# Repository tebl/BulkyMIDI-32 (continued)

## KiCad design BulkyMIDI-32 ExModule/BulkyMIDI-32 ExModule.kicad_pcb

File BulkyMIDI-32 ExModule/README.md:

# BulkyMIDI-32 ExModule
The *BulkyMIDI-32* consists of several separate designs with the same styling, the *ExModule* specifically allows you to use modern Wavetable-modules such as those sold by serdashop.com (not affiliated with this project). Normally these would be installed onto a compatible vintage soundcard, but as it turns out - the machine I wanted to install one on had an AWE32 without the actual header - so instead of changing out the soundcard I built this instead.

What this actually does is add the circuitry that is needed to use them with any MIDI-capable soundcard, externally over a MIDI-cable. Check out the [getting started](https://github.com/tebl/BulkyMIDI-32/blob/main/documentation/getting_started.md) part of the documentation, and while the text mainly covers the *BulkyMIDI-32* (Roland MT-32 emulation via mt32-pi) itself - it's all MIDI, and it should work just about the same. The only difference is that with the *ExModule* you'll be using real modules instead of emulating them.

As for what it looks like inside, there's really not a lot that is needed to make it work - and I was able to assemble most of it thank to the details still available on [atari.joska.no](https://atari.joska.no/db50xg/). While the page focuses on the Atari ST, the specifics are really the same regardless of platform. The source of his designs was based on an article in Elektor Electronics (july/august 1997), but as all of their articles have been permanently locked behind a paywall - I can't link you to a copy of it. In either case I more or less changed just about everything to use similar components as those featured elsewhere in this repository.

**NB!** This module only takes a 5V input, and does not have any way of generating the remaining voltages required by some vintage Wavetable-modules. There are references to a Power-module that could be created to provide those, but I don't have anything to test with it. Unless someone straight up gifts my one of their vintage modules to test with it, it won't be added.

- [1> Building the device](#1-building-the-device)
  - [1.1> Soldering it together](#11-soldering-it-together)
  - [1.2> Without front panel](#12-without-front-panel)
  - [1.3> Including front panel](#13-including-front-panel)
  - [1.4> Finishing touches](#14-finishing-touches)
- [2> Schematic](#2-schematic)
- [3> BOM](#3-bom)

# 1> Building the device
Building a device such as this assumes you have at least minor experience soldering things together, recommended is that you at the very least have access to a soldering station with adjustable temperature. If currently available, you should probably start with 60/40 rosin core solder as the lead-free alternatives tends to be a bit harder to work with.

With requirements for basic equipment sorted, we need to talk a bit about what you want to achieve while building this project. The reason I ask is that while you can build a functional *BulkyMIDI-32 ExModule* by using this module by itself, but there is certainly the option of building the complete version of it - that includes the front panel as well as two faceplates, one that goes on top of the device and one that mounts on the front. 

Now that you know what you want to build, we can get started on the most expensive step in any build process - shopping! So, head on over to the [BOM](#3-bom)-section for some information on what kind of components that you'll need. While I would have liked to give you specific part numbers for "reputable" electronic part suppliers, I can't afford to shop there myself. For that reason I usually make due with what I can find on sites such as ebay, AliExpress and any similar sites that sells affordable Chinese components. The downside to this is that I can't link to a part directly and expect it to stay listed beyond the next couple of days, so you'll need to think of the descriptions listed as *suggested search terms* instead of part numbers.

## 1.1> Soldering it together
The construction of this unit should be fairly straight-forward, just take your time in order to make sure everything goes into place - more or less straight. I usually recommend starting by having a good look at the PCBs, try to figure out where all of the listed components go and in which orientation they go in (most of the information should be clearly marked on the silkscreen).

I will usually try to install components sorted by their physical size, doing it this way means you'll have an easier time keeping everything from looking somewhat crooked. This is your board, your build and you want it perfect - don't you? If you said no, then go sit in the corner because I worked hard on creating this for myself and whoever wants to build one.

Here we've already gotten started by installing all of the resistors needed, making sure that we use the correct values for each position on the board. While doing this, it is always a good recommendation to try and keep the colour bands orientated the same way - mostly because it makes it easier to spot any mistakes later on. The two that goes in the bottom left corner goes to the LEDs, regardless of whether they are mounted here on the front panel. The values for these need to be adjusted according to the type and colour of the LEDs that you are using, in particular when using one that hasn't been dyed to a specific colour - then you will usually need to increase this value to something like 2k2 to avoid blinding yourself by looking at them.

Two different types of diodes are used, the 1N5819 is a Schottky diode and has a silver stripe on it that needs to be matched up with the markings on the board. The 1N4148 diode is probably more familiar to most, it similarly has a black band that instead denotes how to install it on the board.

Sockets should always be installed for the ICs, especially now that there are a lot of bad components floating around. It's always easier to solder something in that it is to remove them, so consider them a cheap insurance. With the sockets in place I've also installed the monolithic disc capacitors, these are all unpolarized and for the ones without any specific markings we will install 100nF capacitors (the code *104* will be printed on them). The single capacitor marked *C3* has a different value from the others, it is 10nF and will have the code *103* printed on it.

The next component we're going to install is a single *2n3906* PNP-transistors, these have a flat side and a round side that needs to be matched to what is printed on the silkscreen. While there are components available that have pre-bent legs matching those on the footprint, I've not come across them at a reasonable price - so I just bend the legs outward myself and firmly push down on them until they sit a bit above the board. They tend to twist a bit when pushing them into place, that is OK to a certain degree and you generally shouldn't force them too much.

Next up are the polarized capacitors, these need to go in the right way for them to function as expected. The stripe on the side of the capacitor denotes the negative side of it, this should be matched up with the filled in area of the footprint. When in doubt, just put the longer pin into the other hole (marked with a "+"). For the most part we won't be anywhere near any relevant voltage ratings, but note that the higher rated ones will generally be physically larger so don't go overboard without measuring - a 16v rating should be enough for our purposes.

Note that the value of capacitor **C2** directly affects the timing of the missing pulse detector, the circuit that ensures that the activity remains solid instead of blinking (as long as we regularly receive data). If you want something that blinks more vigorously, lower the value to *1 uF*. The formula for calculating the timing used is  T = 1.1 * R1 * C2, which for the specified values means that we keep the LED on as long as we don't see any gaps that are longer than 0.33 seconds. Active MIDI keep-alive messages on more modern equipment is commonly sent out intervals of around 300ms, so that is the rationale for choosing a these specific values.

I designed the board for a PJ-307 3.5mm stereo audio sockets, but the similar PJ-317 may be used as well - both of these are common 5-pin sockets sold just about everywhere. While I've preferred to use green ones for audio output in other parts of the *BulkyMIDI-32* project, I didn't have one available and so I used this black one instead. Just don't confuse them with TRS-type A/B MIDI-cables.

Adding the star of the show, the actual Wavetable-header - you may be slightly disappointed by the fact that it is just a segment of dual-row straight pin headers with a 2.54mm spacing. For power we're using a common DC barrel connector (5.5mm x 2.1mm) that have been soldered to the board, it is recommended that you only solder one of the pins at first so that you are able to reheat and reposition it if needed.

Adding the actual MIDI-connectors is next, these are 5-pin DIN connectors that are used for many purposes - they'll be cheaper when not explicitly listed as a "MIDI-connector" (just a tip). Of the two, only the one marked *MIDI IN* is required. The second is marked *MIDI THRU*, it sends out a copy of the same data that was received by this device (without any kind of processing) - installing it allows you to also have a [Channel Monitor](https://github.com/tebl/BulkyMIDI-32/tree/main?tab=readme-ov-file#13-bulkymidi-32-channel-monitor) connected for some nifty effects. 

If you've been following along, there's an empty spot marked *FB1* that could potentially take one of these small wired ferrite cores. I'm not sure if it is needed, but as the analog and digital grounds will have been connected on the modules themselves - I've simply skipped installing them here. That may be a good choice, or a bad one depending on what you're using it with. The good news is that you have the option to choose differently from me if you're able to tell the difference, because I can't.

Depending on your life decisions up to this point, the assembly from this point continues in one of two directions:
- [1.2> Without front panel](#12-without-front-panel)
- [1.3> Including front panel](#13-including-front-panel)

## 1.2> Without front panel
So you resisted the temptation to build the complete version, choosing instead to cut corners where possible? Well, that's OK too! I'm not judging, it was merely just a general observation.

There's not much that we need to do, mainly just install the two 5mm LED (the shorter leg of the LED goes into the hole with the square pad). Also install a right-angle switch.

If you have a faceplate, the board that goes on top of the device, make sure to add some 20mm hex standoffs to each of the four corners before continuing on to with the next part of the build.

- [1.4> Finishing touches](#14-finishing-touches)

## 1.3> Including front panel

The [ExModule Panel](https://github.com/tebl/BulkyMIDI-32/tree/main/BulkyMIDI-32%20ExModule%20Panel) have its own set of documentation going into the various steps required to put it together correctly, a mostly finished unit should look like what is shown above. In particular we need to ensure that the hex standoffs have been aligned so that a *flat* side is lined up with the left and right edges of the board, the nuts on the back needs to have a similar flat side matched to the top and bottom. You may need to trim these slightly with a sharp knife or a file. 

Starting with installing 20mm standoffs to each of the four corners, making sure that these have a *flat* side pointing towards the inside of the PCB. With the alignment correct you should be able to insert the panel into the board without too much force, then your selected top faceplate is installed on top of the boards using temporary screws.

Note that at this point we've not actually soldered them together yet, mostly to ensure that everything comes together correctly before we attempt to actually do so. Push the panel firmly so that it sits towards the back of the cutouts, then solder the pins into place. Afterwards we just trim the excess parts of the pin headers using some proper wire cutters, a flush-cut pair of pliers will usually just break if you use them for pin headers as the metal is too hard for them to reliably work with. When done, I recommend that you reflow all of the joints in case we cracked one of them while cutting of the pins.

When soldered, everything should stay where it is supposed to be. Before continuing on we just remove the faceplate again before moving on to the next step.

- [1.4> Finishing touches](#14-finishing-touches)

## 1.4> Finishing touches

If you've made it this far, you're almost ready to simply start using it. What's missing in order to test it is the actual ICs that needs to be inserted into their sockets, so just get that out of the way before you forget to do so - the indent of the socket should be matched to pin 1 of your ICs, there they will either have a matching indent or a dot next to pin 1.

The device is powered using a 5v DC barrel jack (center positive). Such a power supply should be easy to obtain from your favourite electronics vendor, just make sure that it's from a company that's at least somewhat respected. Personally I'm using a *MEAN WELL GST25B05-P1J*, but that may not be directly applicable to you due to this specific model having been made with a Europlug on it.

At this point in the installation it may be tempting to just plug a Wavetable-module into it and start sending it some MIDI-data, but it may serve you better to be a bit more prudent. Plugging it into power by itself might allow it to blow up by itself instead of taking something *vintage* along with it, then introduce a modern MIDI-interface such as the Roland UM-ONE and have something attempt to send it data - see [getting started](https://github.com/tebl/BulkyMIDI-32/blob/main/documentation/getting_started.md) for something more specific than what'll be provided for in this document. Once you can see that activity lights up according to what can be expected, meaning that it should light up as solid because a modern interface will continuously send it *keep-alive*-messages.

Once satisfied that you're willing to risk a module, connect it up as shown above - preferably the *cheapest*, or just the one you consider easiest to replace! Make sure that you're not offsetting the pins in either of the directions when installing them, I don't know what would happen - but - I assume it won't be a *fun* experience. Repeat tests done earlier, hook up the stereo to an amplifier and you should be able to enjoy some music from your chosen module.

The only step that's remaining is to just screw the faceplates back on the top of the device, replacing those on the front if you have not already done so. With that done we're ready to start planning your next project, maybe a [BulkyMIDI-32 Channel Monitor](https://github.com/tebl/BulkyMIDI-32/tree/main/BulkyMIDI-32%20Channel) for something more exciting to look at or the [BulkyMIDI-32 Play](https://github.com/tebl/BulkyMIDI-32/tree/main/BulkyMIDI-32%20Play) so that you can listen to MIDI-files without a computer attached to it.

# 2> Schematic
The supplied KiCad files should be sufficient as both a schematic and as a  starting point for ordering PCBs (basically you could just zip the contents of the export folder and upload that on a fabrication site), the schematic is also available in [PDF-format](https://github.com/tebl/BulkyMIDI-32/tree/main/documentation/schematic) and this is what you'll need to print and work your way through this things don't work as expected after assembly.

# 3> BOM
Most parts should be easy to get a hold of from your favourite local electronic component shop, but given that I don't have access to such shops where I live so everything was based on whatever I could get cheapest from eBay/AliExpress (free shipping, but plan on waiting 3-4 weeks for delivery). Components in parenthesis are either optional components, or they will only be installed in certain cases such as having functionally been moved to the [front panel](https://github.com/tebl/BulkyMIDI-32/tree/main/BulkyMIDI-32%20ExModule%20Panel). Note that the panel also has its own BOM, make sure to check that out as well when you're ordering parts.

| Reference             | Item                                                              | Count | Order  |
| --------------------- | ----------------------------------------------------------------- | ----- | ------ |
| PCB                   | Fabricate using Gerber files                                      |     1 | [PCBWay](https://www.pcbway.com/project/shareproject/BulkyMIDI_32_ExModule_6564c365.html)
| [Front Panel](https://github.com/tebl/BulkyMIDI-32/tree/main/BulkyMIDI-32%20ExModule%20Panel) | Fabricate using Gerber files                                      |    (1) | [PCBWay](https://www.pcbway.com/project/shareproject/BulkyMIDI_32_ExModule_Panel_8050038f.html)
| [Front Faceplate](https://github.com/tebl/BulkyMIDI-32/tree/main/faceplates/BulkyMIDI-32%20ExModule%20FP1) | Fabricate using Gerber files                                      |    (1) | [PCBWay](https://www.pcbway.com/project/shareproject/BulkyMIDI_32_ExModule_Faceplate_FP1_640ef0bc.html)
| [Top Faceplate](https://github.com/tebl/BulkyMIDI-32/tree/main/faceplates/BulkyMIDI-32%20FB2) | Fabricate using Gerber files                                      |    (1) | PCBWay
| C1,C4,C5,C7,C9        | 100nF (104) ceramic capacitor (5mm)                               |     5 |
| C2                    | 3.3uF electrolytic capacitor (5mm x 2mm)                          |     1 |
| C3                    | 10nF (103) ceramic capacitor (5mm)                                |     1 |
| C6                    | 470uF electrolytic capacitor (8mm x 3.5mm)                        |     1 |
| C8                    | 10uF electrolytic capacitor (5mm x 2mm)                           |     1 |
| D1,D2 *               | 5mm LED, preferably diffused variety                              |    (2)|
| D3                    | 1N4148N small signal diode (DO-35)                                |     1 |
| D4                    | 1N5819 Schottky diode (DO-41)                                     |     1 |
| FB1                   | Wired ferrite core (probably not needed)                          |    (1)|
| J1                    | 2.1mm x 5.5mm barrel plug                                         |     1 |
| J2                    | Dual-row straight pin header                                      |     1 |
| J3,J5                 | Female S-terminal 5pin DIN PCB                                    |  1 (1)|
| J4                    | PJ-307 3.5mm audio connector (5-pin TRS), (alternatively PJ-317)  |     1 |
| Q1                    | 2N3906 PNP-transistor (TO-92)                                     |     1 |
| R1                    | 100k ohm resistor                                                 |     1 |
| R2                    | 10k ohm resistor                                                  |     1 |
| R3                    | 1M ohm resistor                                                   |     1 |
| R4,R5 **              | 470 ohm resistor                                                  |     2 |
| R6,R10,R18            | 220 ohm resistor                                                  |     3 |
| R7                    | 47k ohm resistor                                                  |     1 |
| R8                    | 1k ohm resistor                                                   |     1 |
| R19                   | 2k2 ohm resistor                                                  |     1 |
| SW1 *                 | 6x6x5mm right-angle momentary button                              |    (1)|
| U1                    | 74HCT14 (DIP-14)                                                  |     1 |
| U2,U4                 | 555 (DIP-8)                                                       |     2 |
| U3                    | 6N138 optocoupler (DIP-8)                                         |     1 |
| Mounting ***          | Nylon M3 hex standoffs 20mm (M-F)                                 |     4 |
| Mounting ***          | Nylon M3x6mm nylon screws                                         |     4 |
| Mounting ***          | Nylon M3x6mm nylon nuts                                           |     4 |

*) You can choose to install a front panel, in which case you would skip the installation of the 5mm LEDs as well as the reset switch. Resistors R4/R5 will still be used by the front panel.
**) Resistors are used with LEDs, either installed here or on the front panel. As the choice of LED type and colour dictates the value of resistor, you need to pick something that is suitable here. If using modern bright LEDs, you will need to increase the value to at least 2k2 in order to have something that isn't considered uncomfortably bright.
***) These are available in the form of kits usually advertised *M3 nylon standoff kit* which should contain most of what you'd need. I do however recommend that you pick up extra M-F standoffs of lengths 8mm and 20mm, as quite a lot of them will be used when building more than one module.

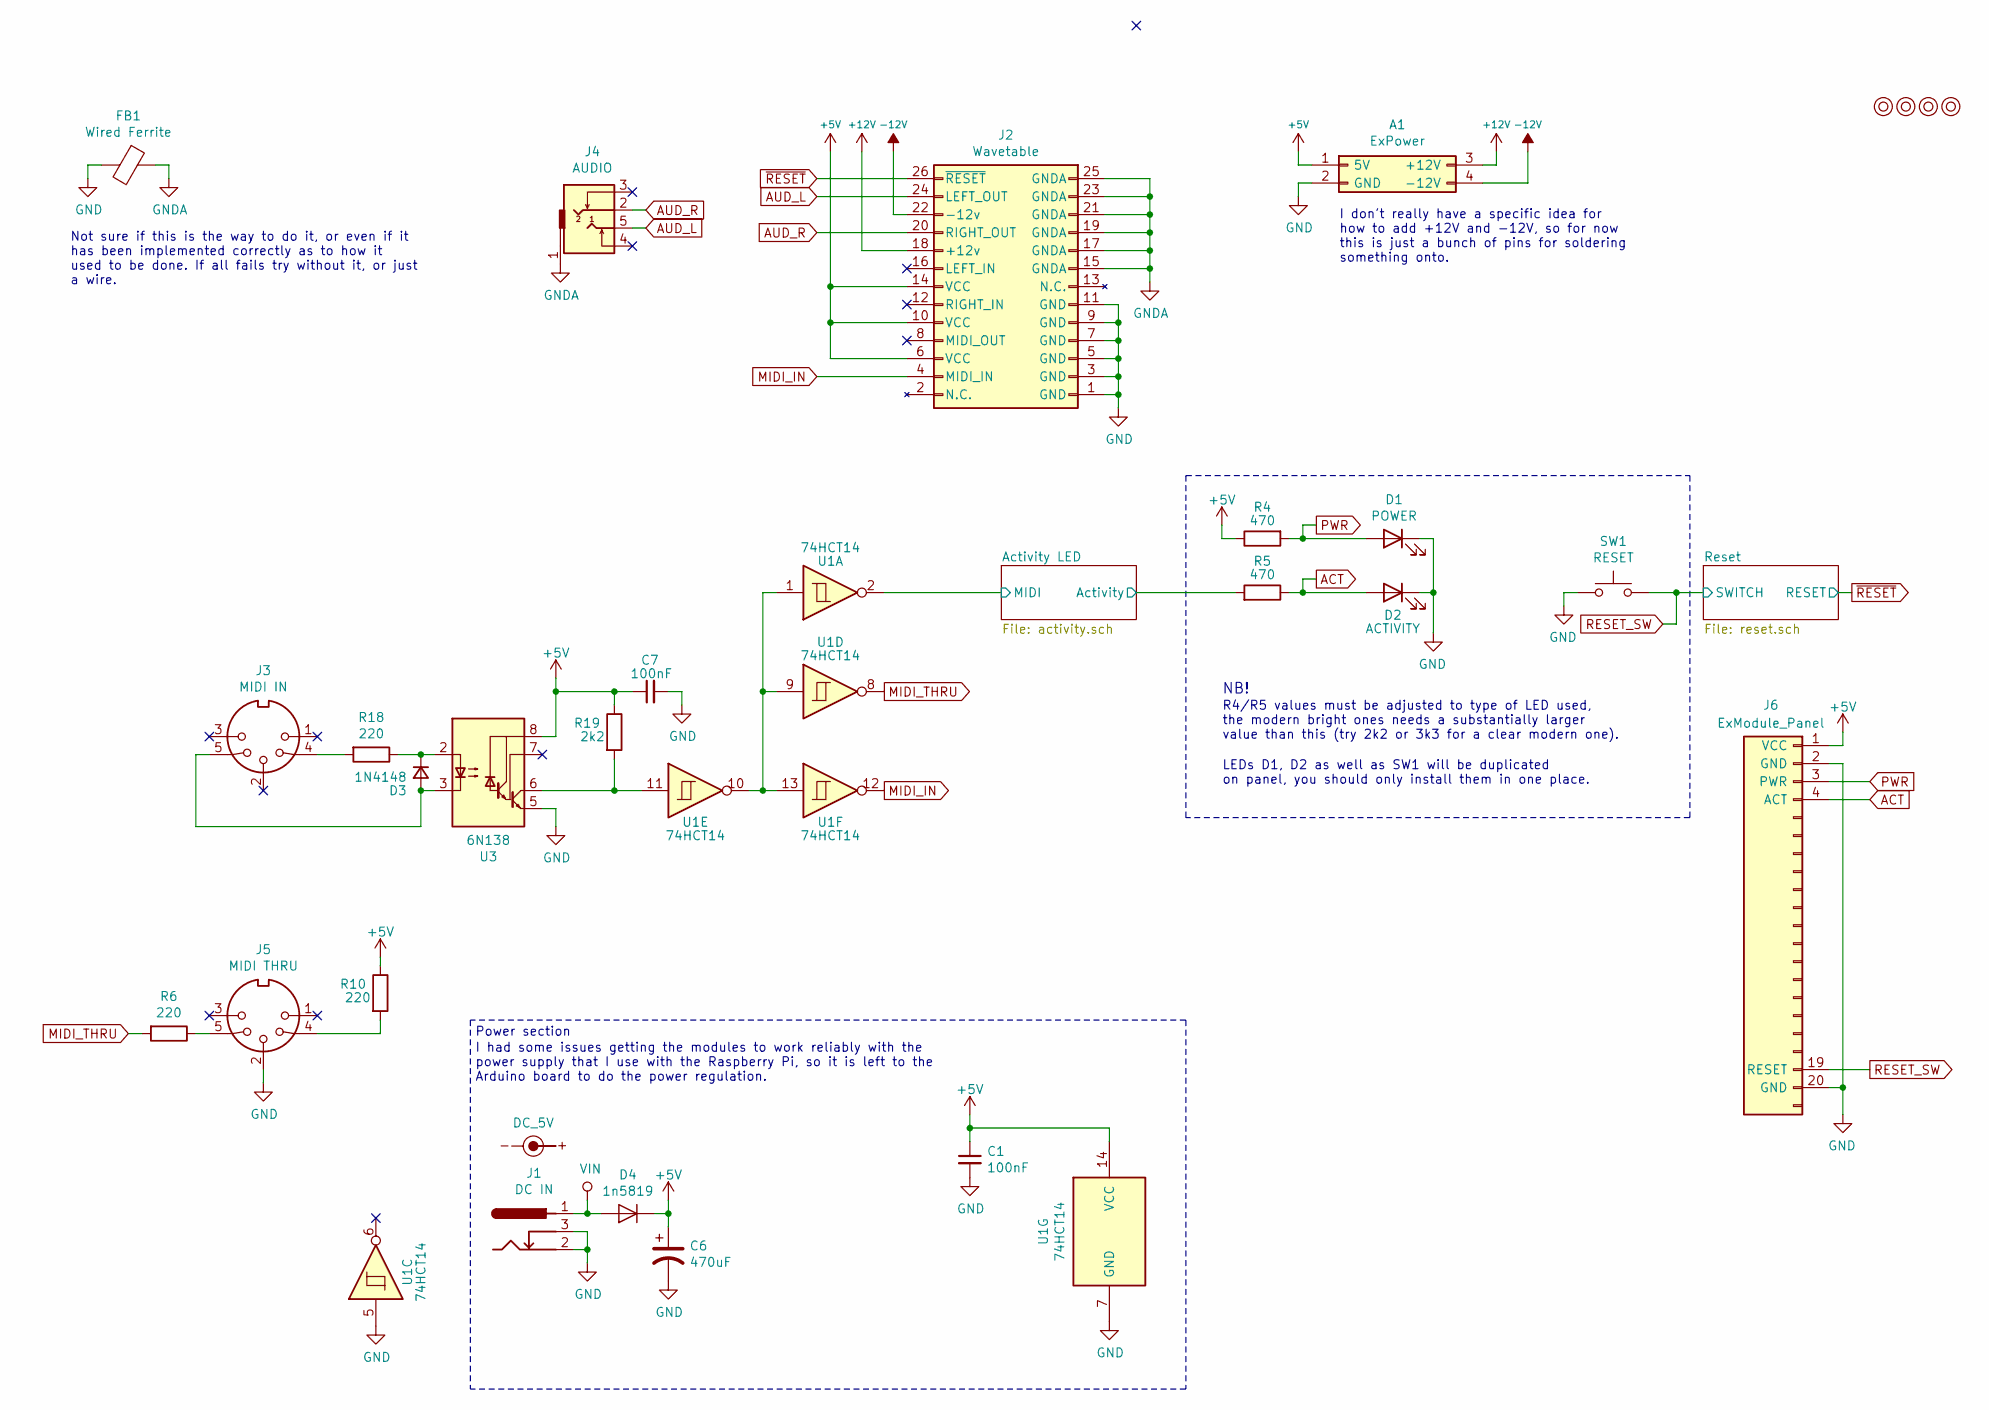
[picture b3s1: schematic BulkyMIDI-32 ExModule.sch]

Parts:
A1: ExPower
C1, C7: 100nF; C_Disc_D4.7mm_W2.5mm_P5.00mm
C6: 470uF; CP_Radial_D8.0mm_P3.50mm
D1: POWER; LED_D5.0mm
D2: ACTIVITY; LED_D5.0mm
D3: 1N4148; D_DO-35_SOD27_P7.62mm_Horizontal
D4: 1n5819; D_DO-41_SOD81_P10.16mm_Horizontal
FB1: Wired Ferrite; L_Axial_L7.0mm_D3.3mm_P10.16mm_Horizontal_Fastron_MICC
J1: DC IN; BARREL_JACK
J2: Wavetable; Wavetable_Header
J3: MIDI IN; DIN5_MIDI_IN
J4: AUDIO; PJ-307_OUT
J5: MIDI THRU; DIN5_MIDI_OUT
J6: ExModule_Panel
M1, M2, M3, M4: Mounting; M3
R4, R5: 470; R_Axial_DIN0207_L6.3mm_D2.5mm_P10.16mm_Horizontal
R6, R10, R18: 220; R_Axial_DIN0207_L6.3mm_D2.5mm_P10.16mm_Horizontal
R19: 2k2; R_Axial_DIN0207_L6.3mm_D2.5mm_P10.16mm_Horizontal
SW1: RESET; SW_Tactile_SPST_Angled_PTS645Vx39-2LFS
SYM1: DC_5V; PWR_Specification
U1: 74HCT14; DIP-14_W7.62mm_Socket_LongPads
U3: 6N138; DIP-8_W7.62mm_Socket_LongPads

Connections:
+5V: A1.1 (5V), C1.1, C6.1, C7.1, D4.1 (K), J2.6 (VCC), J2.10 (VCC), J2.14 (VCC), J6.1 (VCC), R4.1, R10.1, R19.1, U1.14 (VCC), U3.8 (VCC); also elsewhere on the board
+12V: A1.3 (+12V), J2.18 (+12v)
-12V: A1.4 (-12V), J2.22 (-12v)
/Activity LED/Activity: R5.2; also elsewhere on the board
/Activity LED/MIDI: U1.2; also elsewhere on the board
ACT: D2.2 (A), J6.4 (ACT), R5.1
AUD_L: J2.24 (LEFT_OUT), J4.5
AUD_R: J2.20 (RIGHT_OUT), J4.2
GND: A1.2 (GND), C1.2, C6.2, C7.2, D1.1 (K), D2.1 (K), FB1.2, J1.2, J1.3, J2.1 (GND), J2.3 (GND), J2.5 (GND), J2.7 (GND), J2.9 (GND), J2.11 (GND), J5.2, J6.2 (GND), J6.20 (GND), SW1.1, U1.5, U1.7 (GND), U3.5 (GND); also elsewhere on the board
GNDA: FB1.1, J2.15 (GNDA), J2.17 (GNDA), J2.19 (GNDA), J2.21 (GNDA), J2.23 (GNDA), J2.25 (GNDA), J4.1
MIDI_IN: J2.4 (MIDI_IN), U1.12
MIDI_THRU: R6.2, U1.8
unnamed: D3.1 (K), R18.1, U3.2 (C1)
unnamed: D3.2 (A), J3.5, U3.3 (C2)
unnamed: J3.4, R18.2
unnamed: J5.4, R10.2
unnamed: J5.5, R6.1
unnamed: R19.2, U1.11, U3.6 (VO2)
unnamed: U1.1, U1.9, U1.10, U1.13
PWR: D1.2 (A), J6.3 (PWR), R4.2
RESET_SW: J6.19 (RESET), SW1.2; also elsewhere on the board
VIN: D4.2 (A), J1.1
~RESET: J2.26 (~RESET); also elsewhere on the board

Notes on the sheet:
Power section
I had some issues getting the modules to work reliably with the power supply that I use with the Raspberry Pi, so it is left to the Arduino board to do the power regulation.
I don't really have a specific idea for how to add +12V and -12V, so for now this is just a bunch of pins for soldering something onto.
Not sure if this is the way to do it, or even if it has been implemented correctly as to how it used to be done. If all fails try without it, or just a wire.
R4/R5 values must be adjusted to type of LED used, the modern bright ones needs a substantially larger value than this (try 2k2 or 3k3 for a clear modern one).
LEDs D1, D2 as well as SW1 will be duplicated on panel, you should only install them in one place.
NB!

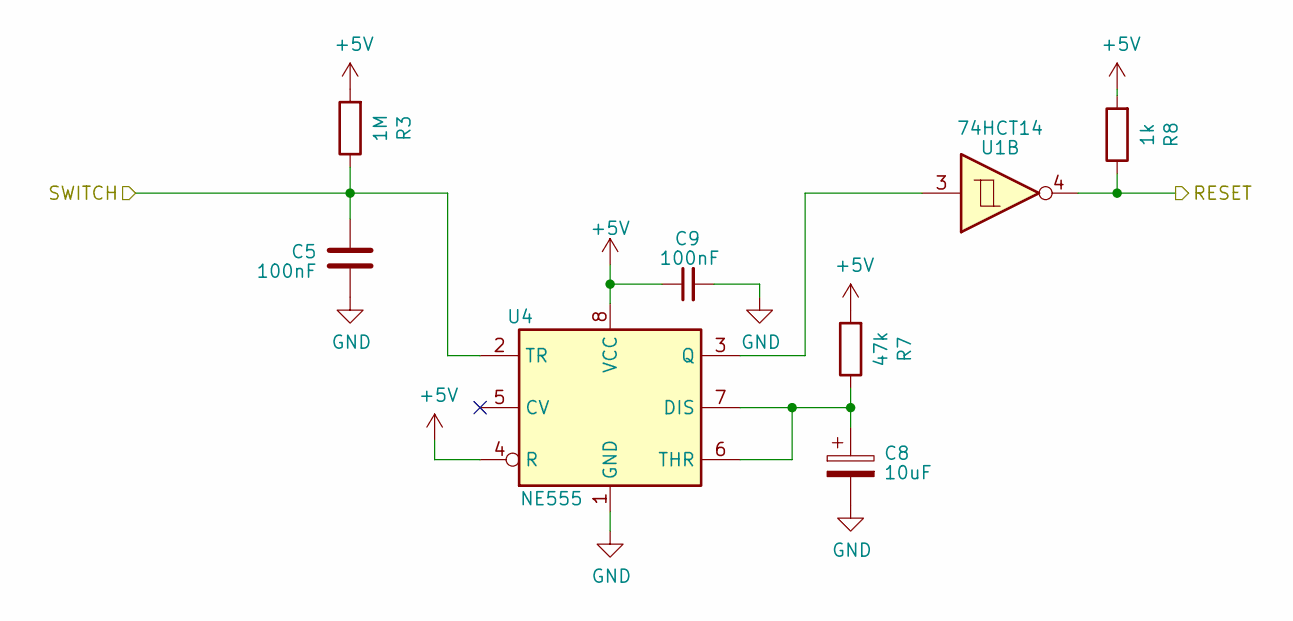
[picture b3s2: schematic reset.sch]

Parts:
C5, C9: 100nF; C_Disc_D4.7mm_W2.5mm_P5.00mm
C8: 10uF; CP_Radial_D5.0mm_P2.00mm
R3: 1M; R_Axial_DIN0207_L6.3mm_D2.5mm_P10.16mm_Horizontal
R7: 47k; R_Axial_DIN0207_L6.3mm_D2.5mm_P10.16mm_Horizontal
R8: 1k; R_Axial_DIN0207_L6.3mm_D2.5mm_P10.16mm_Horizontal
U1: 74HCT14; DIP-14_W7.62mm_Socket_LongPads
U4: NE555; DIP-8_W7.62mm_Socket_LongPads

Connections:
+5V: C9.1, R3.2, R7.2, R8.2, U4.4 (R), U4.8 (VCC); also elsewhere on the board
GND: C5.2, C8.2, C9.2, U4.1 (GND); also elsewhere on the board
unnamed: C8.1, R7.1, U4.6 (THR), U4.7 (DIS)
unnamed: U1.3, U4.3 (Q)
RESET_SW: C5.1, R3.1, U4.2 (TR); also elsewhere on the board
~RESET: R8.1, U1.4; also elsewhere on the board

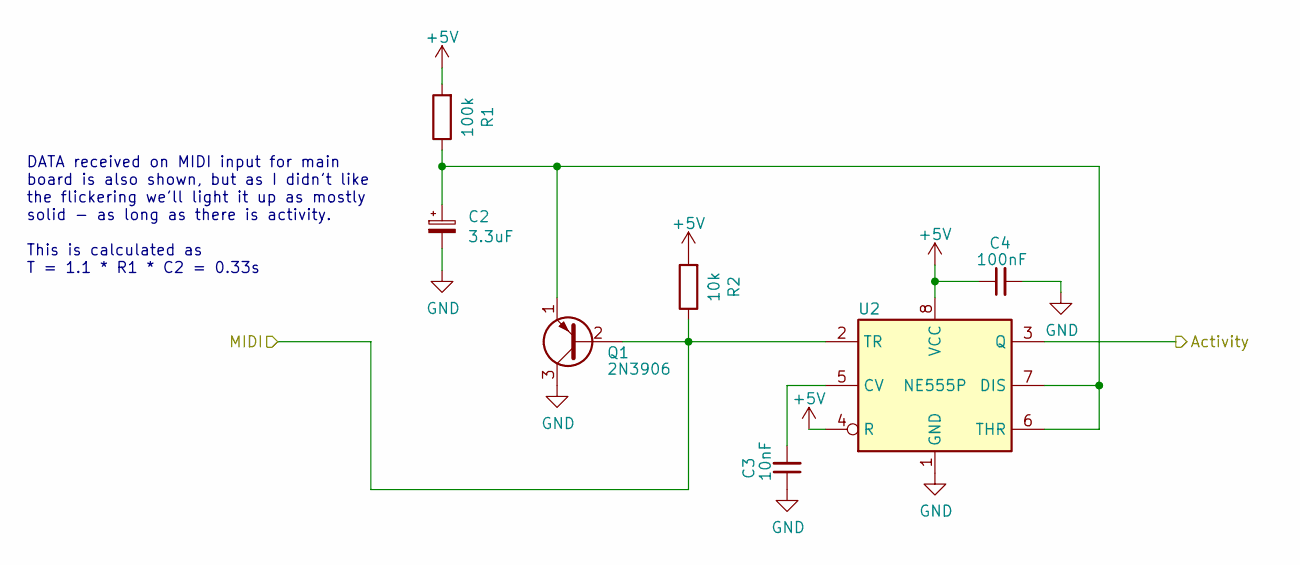
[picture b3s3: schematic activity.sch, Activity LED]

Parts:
C2: 3.3uF; CP_Radial_D5.0mm_P2.00mm
C3: 10nF; C_Disc_D4.7mm_W2.5mm_P5.00mm
C4: 100nF; C_Disc_D4.7mm_W2.5mm_P5.00mm
Q1: 2N3906; TO-92_Inline_Wide
R1: 100k; R_Axial_DIN0207_L6.3mm_D2.5mm_P10.16mm_Horizontal
R2: 10k; R_Axial_DIN0207_L6.3mm_D2.5mm_P10.16mm_Horizontal
U2: NE555P; DIP-8_W7.62mm_Socket_LongPads

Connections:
+5V: C4.1, R1.2, R2.2, U2.4 (R), U2.8 (VCC); also elsewhere on the board
/Activity LED/Activity: U2.3 (Q); also elsewhere on the board
/Activity LED/MIDI: Q1.2 (B), R2.1, U2.2 (TR); also elsewhere on the board
GND: C2.2, C3.1, C4.2, Q1.3 (C), U2.1 (GND); also elsewhere on the board
unnamed: C2.1, Q1.1 (E), R1.1, U2.6 (THR), U2.7 (DIS)
unnamed: C3.2, U2.5 (CV)

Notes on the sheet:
DATA received on MIDI input for main board is also shown, but as I didn't like the flickering we'll light it up as mostly solid - as long as there is activity. This is calculated as T = 1.1 * R1 * C2 = 0.33s

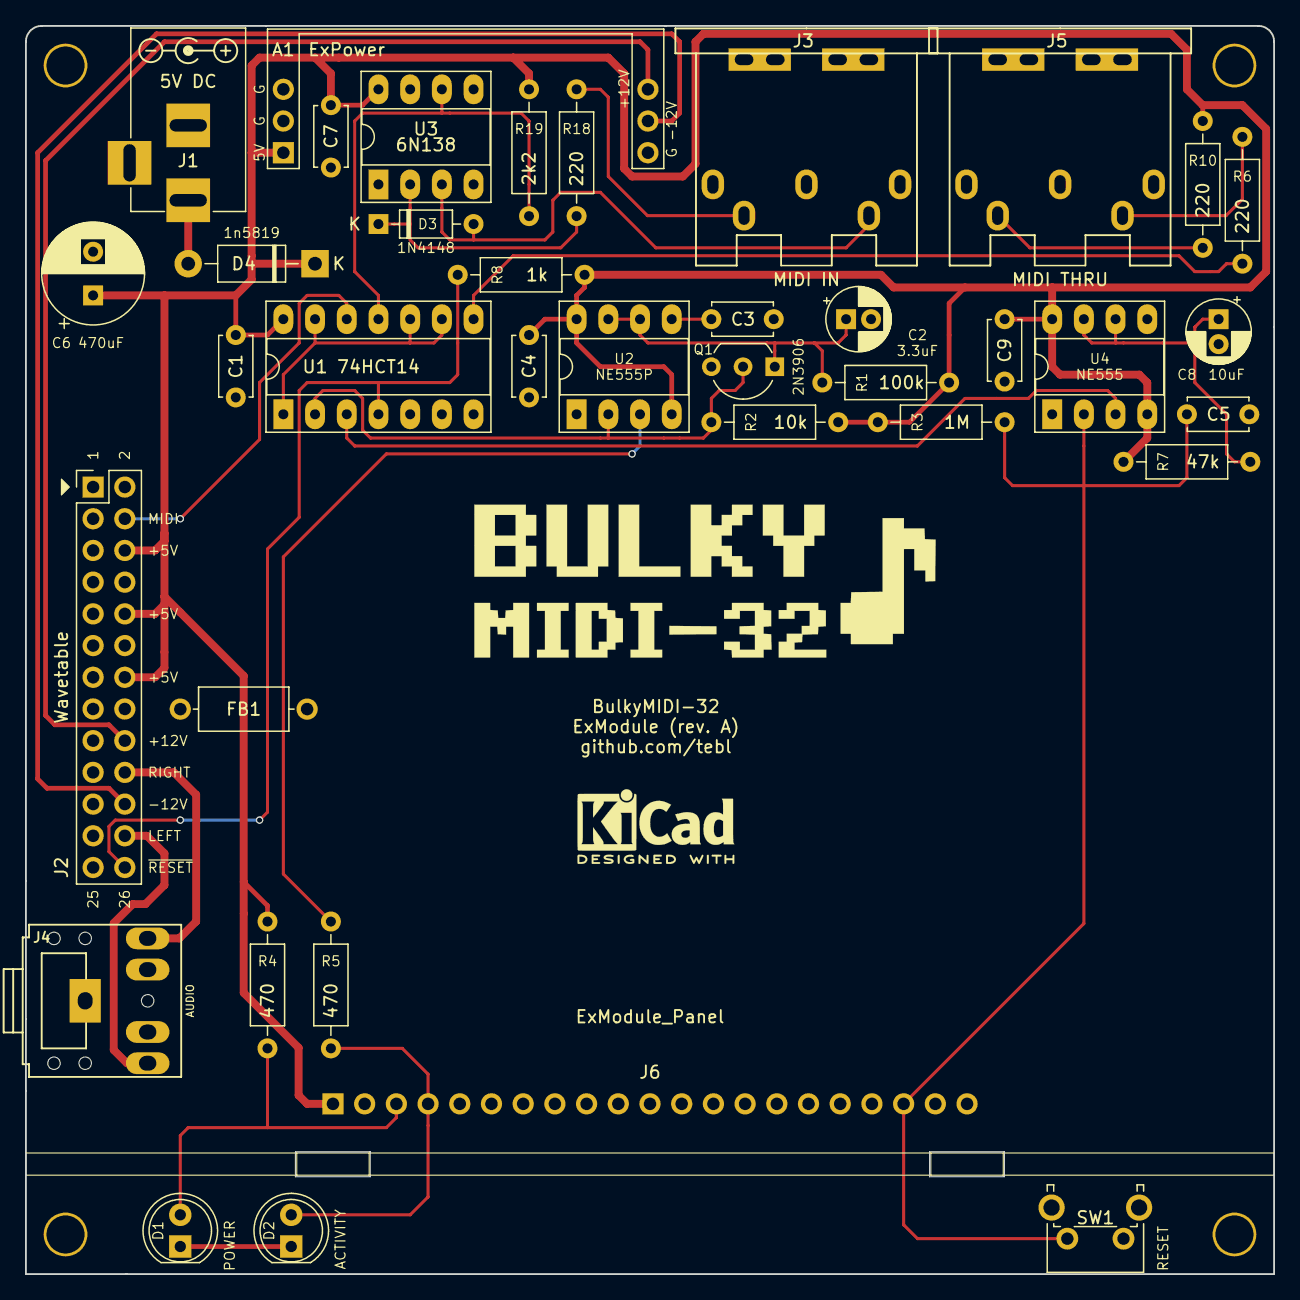
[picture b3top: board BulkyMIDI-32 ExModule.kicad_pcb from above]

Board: 2 copper layers, 100.0 x 100.0 mm, 43 parts (0 on the bottom side), 27 nets.

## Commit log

2022-01-22 And so it begins...
2022-01-23 Schematic drafted
2022-01-23 Changed faceplate connector and PCB size
2022-01-23 Changed DIN to match
2022-01-23 Moved display
2022-01-23 Moved JP1, JP2
2022-01-24 Routed tracks
2022-01-24 Added simple logo
2022-01-24 Faceplate sketched out
2022-01-24 Gerber export
2022-01-25 Simple README
2022-02-07 Fixed faceplate buttons
2022-02-07 Moved faceplates
2022-02-07 Typo in filename
2022-02-08 Add images
2022-02-10 Gameport adapter
2022-02-10 Gameport adapter (IDC connector)
2022-02-11 Changed port cutout to fit Raspberry Pi 4
2022-02-12 Updated documentation
2022-02-12 Slightly recess the switches to allow for front panel
2022-02-12 Rename file
2022-02-12 ScummVM details added
2022-02-12 Reordered images
2022-02-12 Linked up other documents
2022-02-14 Moved adapters into separate folder
2022-02-15 Added extras connector
2022-02-15 Added jumpers to manually link audio to extras
2022-02-17 Start of an extras board (missing parts of circuits)
2022-02-17 Added a vertical rotary encoder module
2022-02-17 Added vertical rotary encoder option
2022-02-17 ... and the rest of the files
2022-02-17 RS232 mounting holes
2022-02-18 Baud rate converter parts
2022-02-18 Routed tracks for extras board
2022-02-18 Fixed RX/TX swapped
2022-02-18 Fixed ERC warning
2022-02-21 Amiga serial adapter
2022-02-21 Schematic
2022-02-24 Debugger at 38400
2022-02-25 Convert pitch to ISO note name
2022-02-26 Pitch bend details
2022-02-26 Named instruments
2022-02-26 Moved transceiver code
2022-03-03 Remove gerber files
2022-03-03 Larger RS232 mounting pads
2022-03-03 Better fit for Raspberry Pi4
2022-03-03 Read configuration
2022-03-03 Add third status LED
2022-03-04 Changed default setting to match expected direction
2022-03-04 Command line interface
2022-03-04 Removed loose track
2022-03-09 Swapped INPUT1/INPUT2 inputs
2022-03-10 Slightly recessed potentiometers
2022-03-10 Better LED naming
2022-03-10 Outline for a backplate
2022-04-02 Rotary encoder note
2022-04-02 Moved input2 to make space for cap
2022-04-02 Add build images
2022-04-05 First build documentation draft
2022-04-05 Add note about extras
2022-04-05 Cleanup
2022-04-07 Reordered IDC pins
2022-04-07 Specify correct MAX232A variant
2022-04-07 Bump version
2022-04-08 Documenting things
2022-04-08 preview picture
2022-04-08 Build images
2022-04-09 Add temporary missing image (need to replace it)
2022-04-09 Update documentation
2022-04-09 Added BOM for extras
2022-04-09 Vertical rotary encoder readme
2022-04-11 Add order links
2022-04-11 ... and fixing it
2022-04-11 Add build section to FA1
2022-04-19 Made DATA LED a bit nicer, moved rotary encoder slightly
2022-04-20 Tweaked silkscreen
2022-05-02 Update build images
2022-05-02 Update image
2022-05-02 Update component map
2022-05-02 Forgot to crop image
2022-05-02 Try again
2022-05-04 Split document
2022-05-04 Fixed images
2022-05-04 Add amiga images
2022-05-04 Add image
2022-05-05 Updated images
2022-05-05 Added getting started section for Amiga
2022-05-06 Adapter README
2022-05-06 Tweak README
2022-05-15 Untested channel module
2022-05-16 Added channel front panel
2022-05-16 Add the start of a README
2022-05-18 VU SIDi schematic
2022-05-19 Untested VU SIDI module
2022-05-19 Added VU SIDi front panel
2022-05-20 Faceplate FA3
2022-05-20 PCB previews
2022-05-20 BA1 cutouts
2022-05-20 BA1 preview
2022-05-20 VU SIDi FP1
2022-05-20 Added Channel FP1
2022-05-23 Add README
2022-05-25 Untested play module
2022-05-26 Added Play Panel
2022-05-26 Update schematic
2022-05-26 Add schematic notes
2022-05-28 Added Play FP1 and a post for holding OLED
2022-05-28 Schematic tweak
2022-05-28 Removed rounded front edges
2022-05-28 ... and the same for faceplates
2022-05-29 Silkscreen tweaks
2022-05-29 Moved components in the way of mounting panel
2022-05-29 Moved audio jacks slightly
2022-05-30 Increase C4/C16 capacity slightly
2022-05-31 Renamed faceplate and removed DIN cutouts
2022-05-31 Add datasheet
2022-05-31 Added driver note
2022-06-07 Channel logo added to FP1, same with Play
2022-06-07 Silkscreen logo tweak
2022-06-09 Channel 2 (MCU edition)
2022-06-16 Build tweaks
2022-06-17 Adjust faceplate cutout for screen
2022-06-18 Wrong capacitor value
2022-06-19 Just getting started
2022-06-20 Functioning on a basic level
2022-06-21 Separate class for LED
2022-06-21 Testing encoder and display
2022-06-21 Read button
2022-06-22 Add intro sequence
2022-06-22 Control brightness
2022-06-22 Activity fade effect
2022-06-22 Only abort intro sequence on expected messages
2022-06-23 Use actual pin
2022-06-23 Off by one bug
2022-06-24 Use ezbutton and custom led class
2022-06-24 Forgotten gate
2022-06-24 font icons
2022-06-24 Try something else
2022-06-25 Remove u8g2 and substitute ssd1306ascii to have enough RAM to work with
2022-06-27 Not working
2022-06-27 Finally plays something
2022-06-28 Control tweaks
2022-06-29 Browse files
2022-06-30 Can loop file
2022-06-30 Adjust tempo
2022-06-30 Added a boot screen
2022-07-08 Make space for front panel
2022-07-08 Center display instead
2022-07-09 Add module panel
2022-07-09 Module FP1 sketched out
2022-07-10 Untested Mk7 adapter
2022-07-10 Add schematic
2022-07-10 Exported files
2022-07-12 Audio switch panel
2022-07-13 Audio Switch schematic
2022-07-14 Untested audio switch module
2022-07-14 Audio Switch FP1
2022-07-18 Use system LED for all changes in player states
2022-07-25 BulkyMIDI-32 FB2
2022-07-25 Moved extras LEDs to match FP1
2022-07-27 Fix weird socket selection
2022-07-28 Slightly adjust screen cutout
2022-07-28 Change R7 value
2022-07-29 Remove temporary file
2022-07-29 Mk7 adapter needs external power
2022-07-29 MIDI Breakout Board
2022-08-01 Simpler VU meter circuit
2022-08-03 Silkscreen tweak
2022-08-03 Changed description
2022-08-03 Modules worked more reliably when run through the onboard regulator
2022-08-04 Update module documentation
2022-08-04 FB2 preview
2022-08-05 Adjust INPUT1/INPUT2 slightly to the right
2022-08-06 Audio Switch entry
2022-08-07 Typo
2022-08-07 Changed BA1 to match new layout
2022-08-07 Add pulldown to breakout board
2022-08-07 Update guide
2022-08-08 Update revision details
2022-08-09 Slight text tweaking
2022-08-21 Migrate to Arduino Pro Micro and max232 due to chinesium modules
2022-08-21 File export
2022-09-01 Add diode to keep pro micro from trying to power main module
2022-09-01 Changes to make it run on Pro Micro
2022-09-01 Small fiddling
2022-09-03 Transceiver mode now just shuffles bytes directly
2022-09-03 Moved MIDI debugging code into separate sketch
2022-09-03 Play around with LED settings
2022-09-04 Update images
2022-09-05 Added second diode just in case
2022-09-05 Update component overview
2022-09-05 Fix border
2022-09-05 Add small notes
2022-09-06 DOSMID
2022-10-04 Added alternate output placement
2022-10-04 Schematic draft for input switch
2022-10-04 The actual files
2022-10-05 Initial layout done
2022-10-05 Add Input Switch (FP1)
2022-10-06 Update PCB fabrication links
2022-10-15 Move cutout up 0.5mm
2023-01-28 Tweak footprints to show direction and adapt 3.5mm footprint for PJ-317
2023-01-28 Faceplate for use without extras-board
2023-01-28 Add some documentation
2023-01-28 Update connectors
2023-02-02 Prototype for BulkyMIDI-32 for installation in PC drive bay
2023-02-02 Remove leftover files
2023-02-05 Untested wavetable adapter
2023-02-07 Internal faceplate
2023-02-10 Add some images
2023-02-10 Update Amiga README
2023-02-13 Better accomodate for wider PCBWay board widths
2023-02-15 Untested TRS to MIDI-adapter
2023-03-08 Add videos
2023-12-02 Untested boards for MiniDexed software
2024-03-21 Dexed changes
2024-03-21 Small changes to internal layout
2024-03-21 Updated display footprint
2024-03-21 Added little nubs to PJ-307 footprint
2024-03-23 Small tweaks
2024-04-03 Some sound cards with external Wavetable-header
2024-04-05 Power switch (very untested)
2024-04-05 Incomplete ExModule
2024-04-06 Add activity
2024-04-06 ExPower symbol
2024-04-06 ExModule layout
2024-04-06 Add ExModule panel
2024-04-06 ExModule faceplate
2024-04-07 Power switch faceplate
2024-04-07 Add order position
2024-04-07 Use real name before I forget
2024-04-07 Add order number placeholder
2024-04-07 Export files
2024-04-20 Input Switch README
2024-04-20 Input Switch Panel README
2024-04-20 Reference to Input Switch FP2
2024-04-20 Update youtube images
2024-04-21 Tweak documentation
2024-04-24 ExModule build images
2024-04-30 Fixes panel errors and inconsistencies
2024-04-30 PowerSwitch sketch
2024-05-24 Updated Power Switch to incorporate changes
2024-05-25 ExModule Panel README
2024-05-26 ExModule README
2024-05-26 Remove link to the wrong thing
2024-05-29 Shared project URLs
2024-06-06 Ko-fi
2024-10-01 Updated Power Switch
2024-10-01 Add video
2025-03-21 Long press shows menu icons, allowing looping as before as well as automatically playing the next file found
2025-03-24 Autoplay now has gap between tracks
2025-03-24 Setting to enable wraparound on autoplay
2025-03-24 Use LEDs more, uncomment setting to disable
